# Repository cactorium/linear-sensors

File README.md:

# Linear PCB sensors
This will eventually contain the sensing mechanisms for several different types of digital calipers.
Luckily the patents on all of them have run out, so I can copy a lot of the exact details used in existing calipers, which should mean there's a lot of a better chance of getting good results out of this.
The designs will be made in KiCAD, and will be under a sufficiently liberal license for you guys to use for whatever.
Hopefully these will be cheap and easy enough to use for a lot of interesting applications, like close looping the axes on 3D printers for a lot cheaper than the $1k+ optical scales that's used on higher end models right now.

**NOTE: the schematic and PCB are now in KiCAD 5. I don't know how backwards compatible it is with older version of KiCAD**

## Capacitance-based sensor v1
~The capactive sensor appears to be working right now, with a sample rate of 96 samples/sec and a precision of about ~ +-0.06 mm (~ +-0.002in), limited by noise.
The accuracy appears to stay within +- 0.01mm for a lot of the range, but the inaccuracy increases at various points (and also if you're touching the scale) along its range.
It's currently affected moderately strongly by mains noise, the next revision will add better filtering to the front end to reduce this issue.~
So the signal is actually incredibly accurate, as long as the surfaces are closely mating and the amplifier isn't clipping.
I'm getting about ~0.002 mm precision (still need to check accuracy across the full range) after carefully adjusting gain to remove clipping.
The signal doesn't appear anything near a sine wave at the output, it mainly consists of a lot of sharp spikes that I guess the FIRs turn into something closer to a sine wave.
It's currently probably limited by the numerical accuracy of the arctangent operation in the processing, but I need to do more testing to see how accurate it is across its range before tuning its precision any more.

There also appear to be some large inaccuracies across its full range, which also I'm currently working out.

## Capacitance-based sensor v2
I reduced the width of the scale by half to try to improve the form factor and added a second stage of filtering to try to reduce its susceptibility to noise.
I removed the large metallic layer that used to overlap the receiving pad to see if that would reduce the amount of noise.
I'm pretty sure covering it with ground will reduce the output signal by adding a lot of parasitic capacitance, so right now it's bare aside from a trace to get the signal from the receiving pad.
There's now three stages of amplification, the first one, which is adjustable and has a gain from 1x to 10x, and two fixed stages which are 2x and ~10x respectively.
There's several stages of low pass and high pass filtering throughout all this, plus some bypass resistors in case this all turns out wrong so I can revert to the v1 analog circuitry in the worst case.
The edges of the PCB were also rounded just to make it look a little nicer, and the mounting holes are now evenly spaced to make mechanical stuff a lot easier to work out.

The BOM cost is about $16, which is pretty reasonable, but I'll probably try to get it a little lower next revision.

The extra filter does appear to work very nicely; the output actually looks like a sine wave, so it might be possible to remove some of the digital filtering while maintaining the same accuracy, but I'm going to work on mechanically stabilizing the setup to get more repeatable measurements.
It does appear to be noticeably better just from rough observations; it takes a lot less effort to get the measurement to where it's bouncing around +- 0.001mm compared with the first revision.
I'm guessing the next revision will focus on improving the form factor and cost.

TODO: add pictures

## How they work
Right now I'm looking at two major designs, inductively coupled ones, developed by Mitutoyo, and the T-shaped capacitively coupled ones used in most cheap caliper designs by Mauser-Werke Oberndorf GmbH.
In both cases, the basic gist is that there's a pattern on the stationary bit (called the stator) that affects its coupling with the bit that moves (let's call it the rotor), and in both cases a phase measurement based on measurements as a result of this coupling is used to get a fine measurement, while a counter is used to keep track of how many times the phase has gone about 360 degrees, giving a coarse measurement.
The actual measurement is simply the sum of these two measurements.

In the Mitutoyo design, a pulse is sent into a transmitting coil, which causes it to resonate.
The EM waves produced by this coil are coupled into a pair of receiving coils.
The receiving coils are shaped so that normally the EM waves perfectly cancel out, but the presence and displacement of the disruptors in the stator cause the cancellation to be incomplete.
The receiving coils are shaped so that they form a sine and cosine wave with respect to the displacement relative to the stator.
The receiving coils resonate in series with a capacitor, and a switch is used to stop the resonation near when the voltage across the capacitor is at its peak.
Then the voltage across the capacitors are read using an ADC, and that's used to calculate the displacement within a single stator period.
A counter's used to get the coarser measurement when the stator's moved greater than one period.

In the Mauser-Werke Oberndorf design, there's many transmitting electrodes, each at a different phase.
Each one is shifted by the same amount relative to the one before it.
In the original design, they formed a set of three before it repeated, with relative phases of 0, 120, 240 degrees.
Modern designs tend to use a set of 8, so that's what we'll use here.
These transmitting electrodes couple with the middle of the tee in the stator design, so that the signal read off the T electrode is effectively the capcitively weighted sum of the electrodes that are coupled (physically over) it.
Shifting the rotor causes the ratios to change, allowing an (very good) approximately linear change in phase for a given displacement.
The wider sections of the T are capactively coupled with a receiving electrode on the rotor, and this is filtered and fed into a zero crossing detector to determine the phase different compared with the input signal, giving you a fine measurement of displacement.
The coarse measurement is found by counting, as in the Mitutoyo case.

TODO add patents to repository

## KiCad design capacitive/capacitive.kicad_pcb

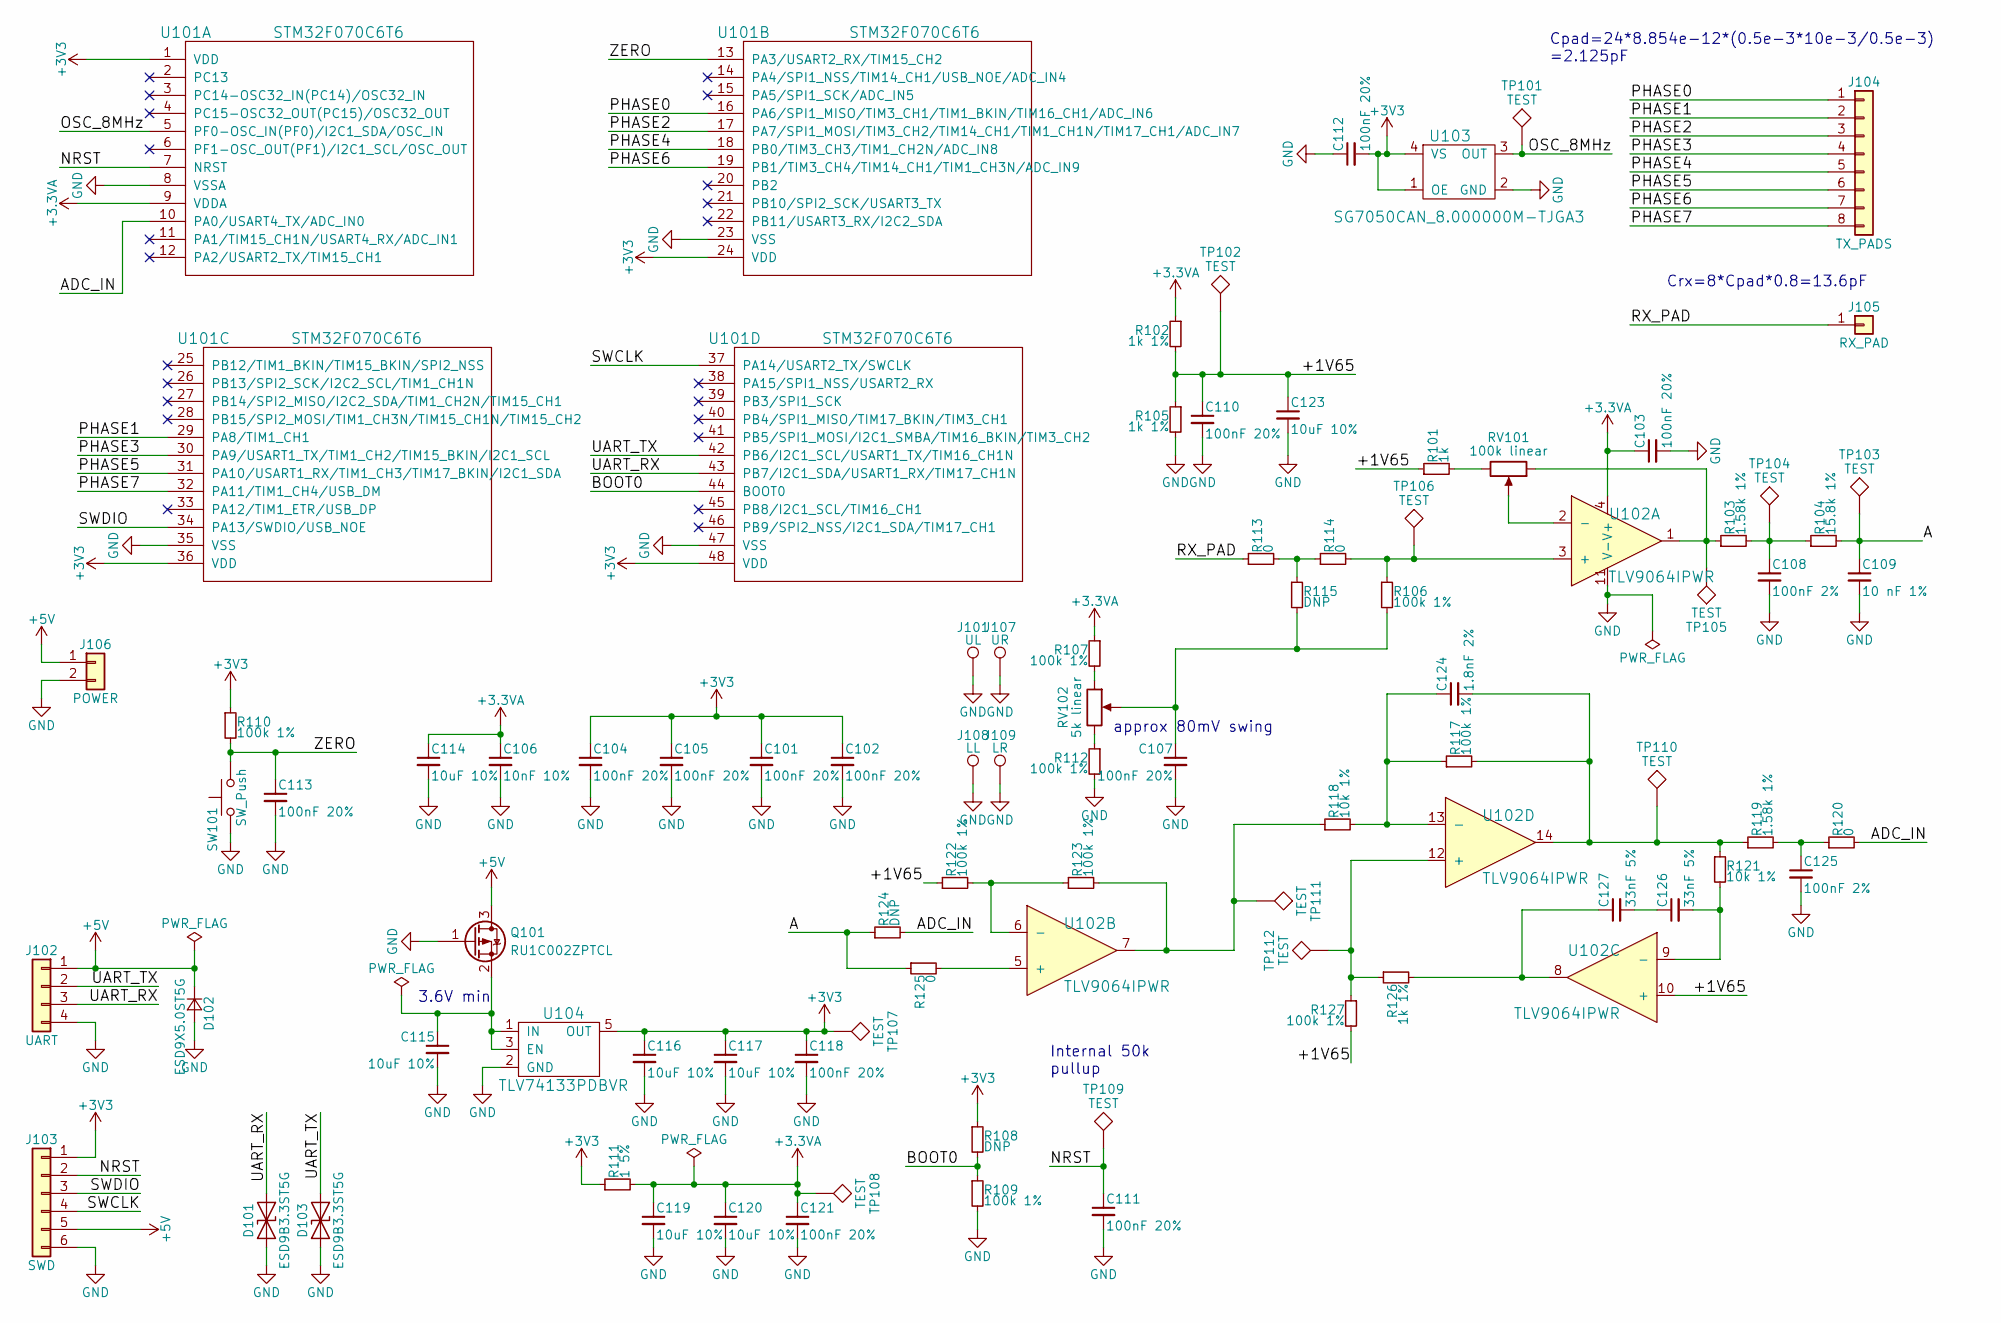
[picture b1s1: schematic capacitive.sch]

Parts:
C101, C102, C103, C104, C105, C107, C110, C111, C112, C113, C118, C121: 100nF 20%; C_0805_HandSoldering; Mouser 710-885012207016
C106: 10nF 10%; R_0603_HandSoldering; Mouser 80-C0603C103M5RAUTO
C108, C125: 100nF 2%; C_1210_HandSoldering; Mouser 667-ECH-U1C104GX5
C109: 10 nF 1%; C_0805_HandSoldering; Mouser 81-GRM2195C1H103FA1D
C114, C115, C116, C117, C119, C120, C123: 10uF 10%; C_1210_HandSoldering; Mouser 581-TAJB106K020RNJV
C124: 1.8nF 2%; C_0603_HandSoldering; Mouser 81-GRM1885C1H182GA1D
C126, C127: 33nF 5%; C_0603_HandSoldering; Mouser 80-C0603C333J4RECLR
D101, D103: ESD9B3.3ST5G; SOD-923; Mouser 863-ESD9B3.3ST5G
D102: ESD9X5.0ST5G; SOD-923; Mouser 863-ESD9X5.0ST5G
J101: UL; Slide_Drill_Left; Mouser NoPart
J102: UART; Socket_Strip_Straight_1x04_Pitch2.54mm; Mouser 855-M20-9990445
J103: SWD; Socket_Strip_Straight_2x03_Pitch2.54mm_SMD; Mouser 855-M20-8750342
J104: TX_PADS; Mouser NoPart
J105: RX_PAD; Mouser NoPart
J106: POWER; Power_Pads; Mouser NoPart
J107: UR; Slide_Drill_Right; Mouser NoPart
J108: LL; Slide_Drill_Left; Mouser NoPart
J109: LR; Slide_Drill_Right; Mouser NoPart
Q101: RU1C002ZPTCL; Rohm_UMT3F; Mouser 755-RU1C001ZPTL
R101: 1k; R_0603_HandSoldering; Mouser 71-CRCW0603100RFKEAC
R102, R105, R126: 1k 1%; R_0402; Mouser 71-CRCW04021K00FKEDC
R103, R119: 1.58k 1%; R_0603_HandSoldering; Mouser 660-RN73H1JTD1581D25
R104: 15.8k 1%; R_0805_HandSoldering; Mouser 71-CRCW12060000Z0EAC
R106, R107, R109, R110, R112, R117, R122, R123, R127: 100k 1%; R_1206_HandSoldering; Mouser 71-CRCW1206100KFKEAC
R108, R115, R124: DNP; R_0603_HandSoldering; Mouser 71-RCS06030000Z0EA
R111: 1 5%; R_0603_HandSoldering; Mouser 755-ESR03EZPJ1R0
R113, R114, R120, R125: 0; R_0805_HandSoldering; Mouser 71-CRCW12060000Z0EAC
R118, R121: 10k 1%; R_0402; Mouser 71-CRCW040210K0FKEDC
RV101: 100k linear; Vishay_T73YE; Mouser 72-T70YE-100K
RV102: 5k linear; Bourns-PVG5H; Mouser 81-PVG5H502C03B00
SW101: SW_Push; LL3301NF065QG; Mouser 612-LL3301NF065QG
TP101, TP102, TP103, TP104, TP105, TP106, TP107, TP108, TP109, TP110, TP111, TP112: TEST; Measurement_Point_Round-SMD-Pad_Small; Mouser NoPart
U101: STM32F070C6T6; ST_LQFP48; Mouser 511-STM32F070C6T6
U102: TLV9064IPWR; TI_TSSOP14; Mouser 595-TLV9064IPWR
U103: SG7050CAN_8.000000M-TJGA3; Crystal_SMD_7050-4pin_7.0x5.0mm; Mouser 732-7050CA8.00TJGA3
U104: TLV74133PDBVR; SOT-23-5_HandSoldering; Mouser 595-TLV74133PDBVR

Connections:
+3.3VA: C103.1, C106.1, C114.1, C119.1, C120.1, C121.1, R102.1, R107.1, R111.2, TP108.1, U101.9 (VDDA), U102.4 (V+)
+3V3: C101.1, C102.1, C104.1, C105.1, C112.2, C116.1, C117.1, C118.1, J103.1, R108.1, R110.1, R111.1, TP107.1, U101.1 (VDD), U101.24 (VDD), U101.36 (VDD), U101.48 (VDD), U103.1 (OE), U103.4 (VS), U104.5 (OUT)
+5V: D102.1 (K), J102.1, J103.5, J106.1, Q101.3 (D)
/+1V65: C110.1, C123.1, R101.1, R102.2, R105.1, R122.1, R127.2, TP102.1, U102.10 (+)
/A: C109.1, R104.2, R124.1, R125.1, TP103.1
/ADC_IN: R120.2, R124.2, U101.10 (PA0/USART4_TX/ADC_IN0)
/BOOT0: R108.2, R109.1, U101.44 (BOOT0)
/NRST: C111.1, J103.2, TP109.1, U101.7 (NRST)
/OSC_8MHz: TP101.1, U101.5 (PF0-OSC_IN(PF0)/I2C1_SDA/OSC_IN), U103.3 (OUT)
/PHASE0: J104.1, U101.16 (PA6/SPI1_MISO/TIM3_CH1/TIM1_BKIN/TIM16_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)
/PHASE1: J104.2, U101.29 (PA8/TIM1_CH1)
/PHASE2: J104.3, U101.17 (PA7/SPI1_MOSI/TIM3_CH2/TIM14_CH1/TIM1_C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)
/PHASE3: J104.4, U101.30 (PA9/USART1_TX/TIM1_CH2/TIM15_BKIN/I2C1_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)
/PHASE4: J104.5, U101.18 (PB0/TIM3_CH3/TIM1_CH2N/ADC_IN8)
/PHASE5: J104.6, U101.31 (PA10/USART1_RX/TIM1_CH3/TIM17_BKIN/I2C1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)
/PHASE6: J104.7, U101.19 (PB1/TIM3_CH4/TIM14_CH1/TIM1_CH3N/ADC_IN9)
/PHASE7: J104.8, U101.32 (PA11/TIM1_CH4/USB_DM)
/RX_PAD: J105.1, R113.1
/SWCLK: J103.4, U101.37 (PA14/USART2_TX/SWCLK)
/SWDIO: J103.3, U101.34 (PA13/SWDIO/USB_NOE)
/UART_RX: D101.1 (A1), J102.3, U101.43 (PB7/I2C1_SDA/USART1_RX/TIM17_CH1N)
/UART_TX: D103.1 (A1), J102.2, U101.42 (PB6/I2C1_SCL/USART1_TX/TIM16_CH1N)
/ZERO: C113.1, R110.2, SW101.1, U101.13 (PA3/USART2_RX/TIM15_CH2)
GND: C101.2, C102.2, C103.2, C104.2, C105.2, C106.2, C107.2, C108.2, C109.2, C110.2, C111.2, C112.1, C113.2, C114.2, C115.2, C116.2, C117.2, C118.2, C119.2, C120.2, C121.2, C123.2, C125.2, D101.2 (A2), D102.2 (A), D103.2 (A2), J101.1, J102.4, J103.6, J106.2, J107.1, J108.1, J109.1, Q101.1 (G), R105.2, R109.2, R112.2, SW101.2, U101.8 (VSSA), U101.23 (VSS), U101.35 (VSS), U101.47 (VSS), U102.11 (V-), U103.2 (GND), U104.2 (GND)
unnamed: C107.1, R106.2, R115.2, RV102.2
unnamed: C108.1, R103.2, R104.1, TP104.1
unnamed: C115.1, Q101.2 (S), U104.1 (IN), U104.3 (EN)
unnamed: C124.1, R117.1, R118.2, U102.13 (-)
unnamed: C124.2, R117.2, R119.1, R121.1, TP110.1, U102.14
unnamed: C125.1, R119.2, R120.1
unnamed: C126.1, C127.2
unnamed: C126.2, R121.2, U102.9 (-)
unnamed: C127.1, R126.2, U102.8
unnamed: R101.2, RV101.3
unnamed: R103.1, RV101.1, TP105.1, U102.1
unnamed: R106.1, R114.2, TP106.1, U102.3 (+)
unnamed: R107.2, RV102.1
unnamed: R112.1, RV102.3
unnamed: R113.2, R114.1, R115.1
unnamed: R118.1, R123.2, TP111.1, U102.7
unnamed: R122.2, R123.1, U102.6 (-)
unnamed: R125.2, U102.5 (+)
unnamed: R126.1, R127.1, TP112.1, U102.12 (+)
unnamed: RV101.2, U102.2 (-)

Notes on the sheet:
3.6V min
Cpad=24*8.854e-12*(0.5e-3*10e-3/0.5e-3) =2.125pF
Crx=8*Cpad*0.8=13.6pF
Internal 50k pullup
approx 80mV swing

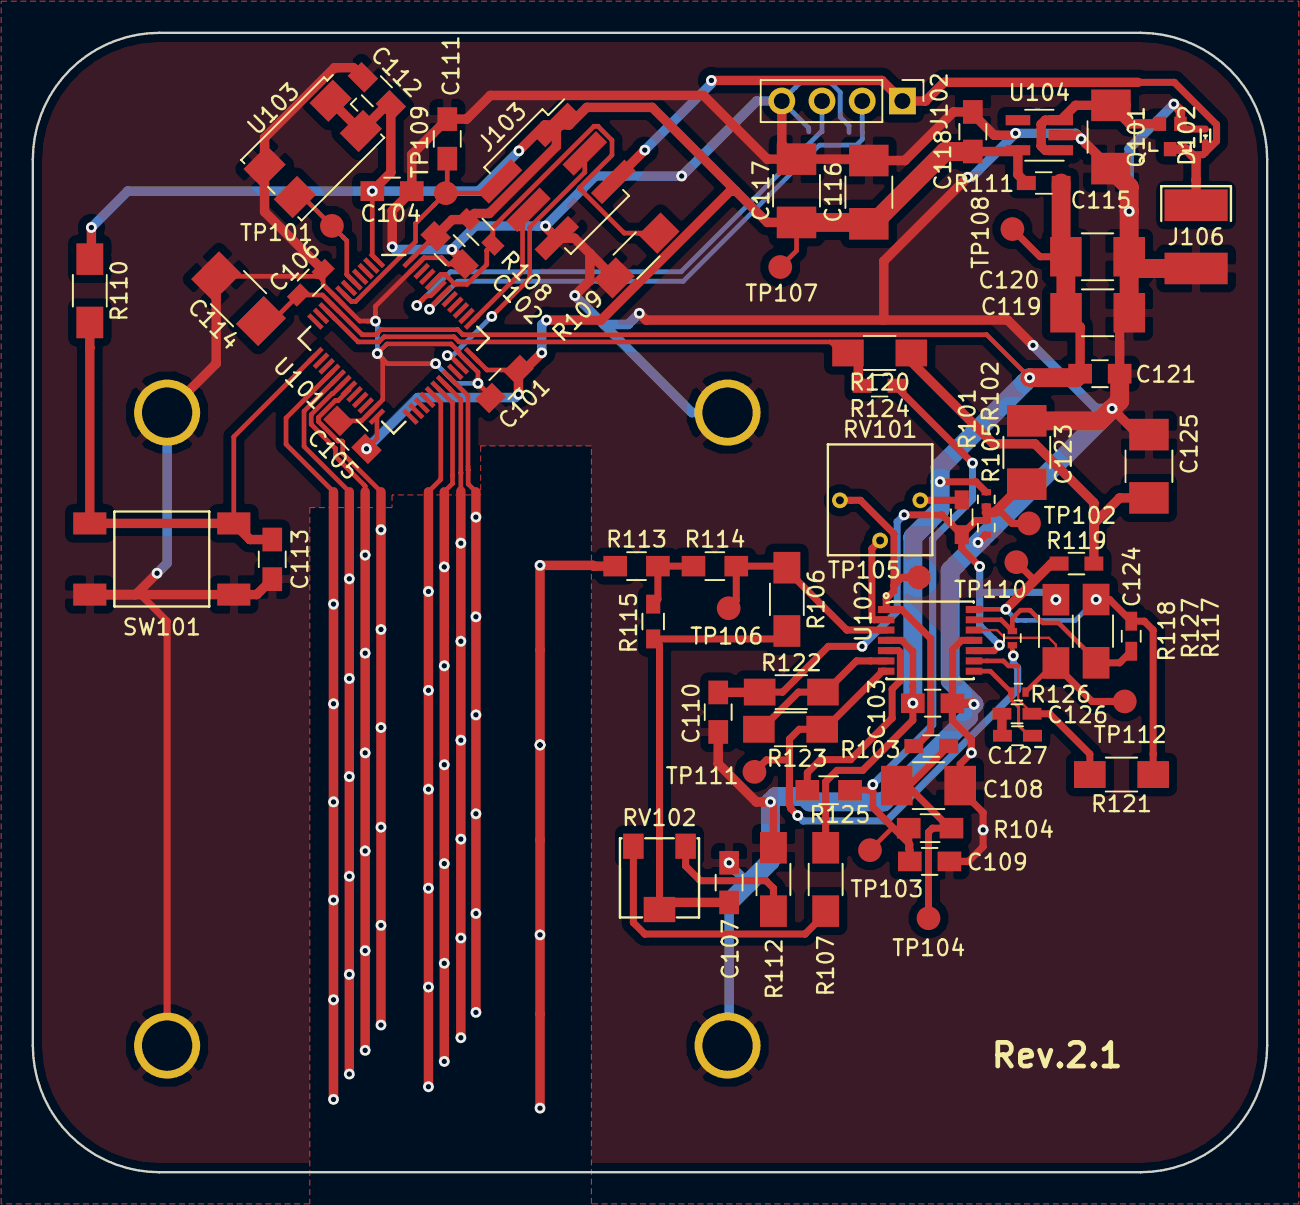
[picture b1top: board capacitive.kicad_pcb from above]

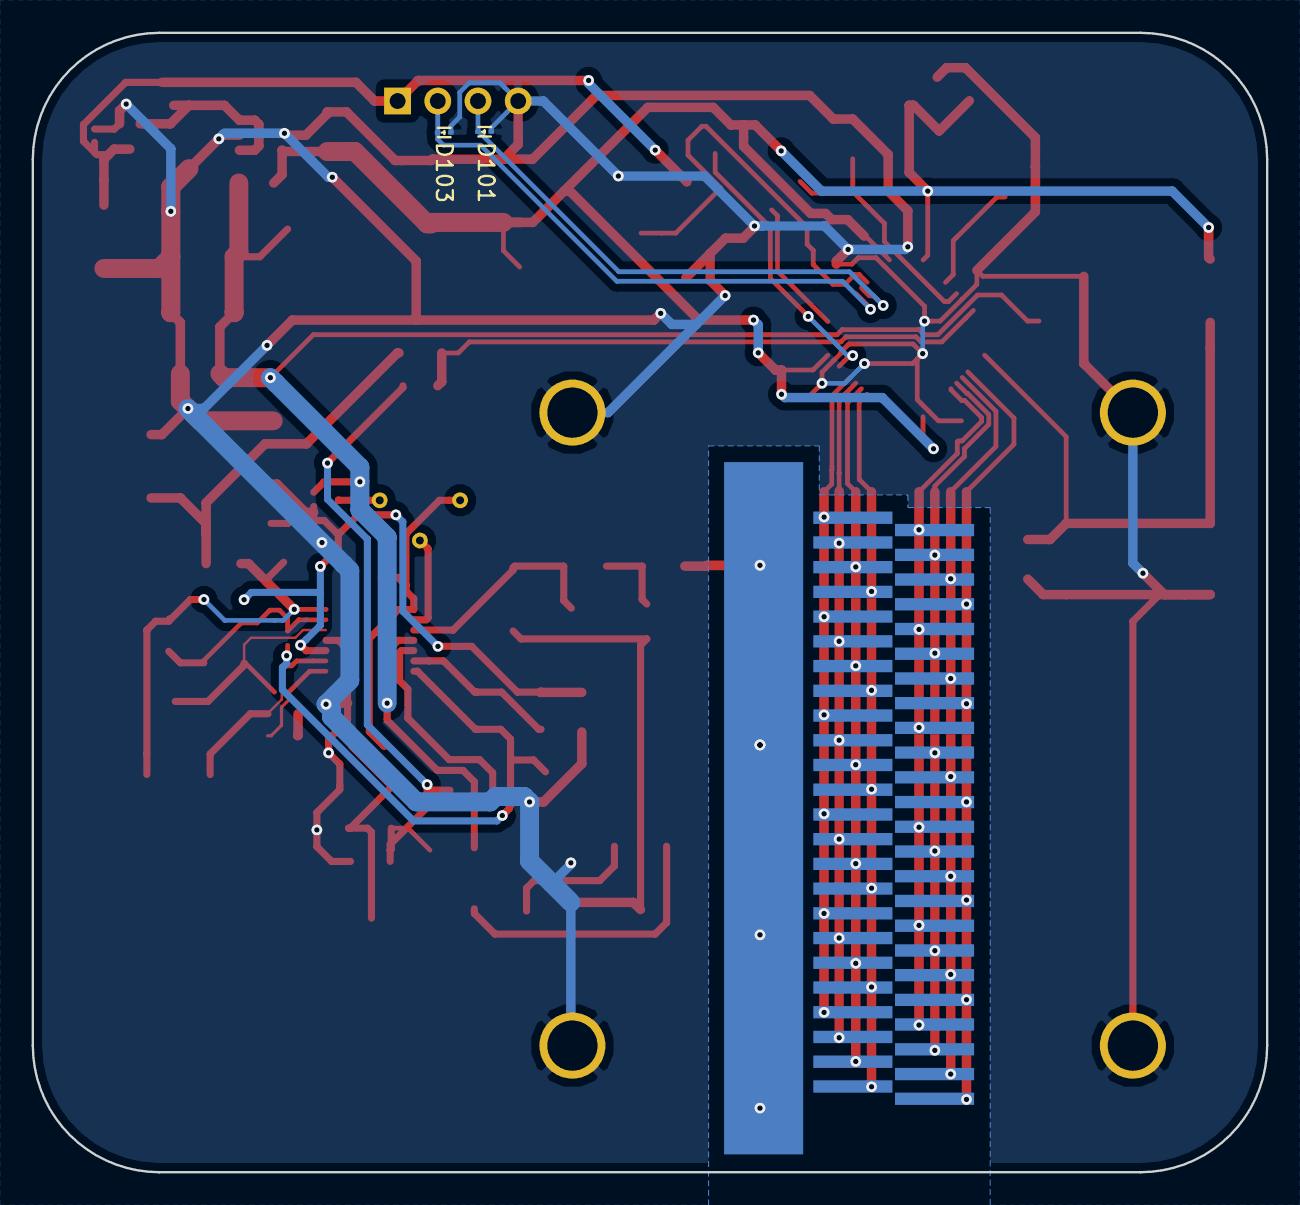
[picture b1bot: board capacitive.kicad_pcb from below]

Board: 2 copper layers, 78.0 x 72.0 mm, 84 parts (4 on the bottom side), 44 nets.

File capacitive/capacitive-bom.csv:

Reference,Quantity,Identifier,Package,Value,Tolerance,Voltage,Current,Power,PN,Mouser
"U101","1","","","STM32F070C6T6","","","","","","511-STM32F070C6T6"
"C111;C103;C110;C101;C104;C105;C102;C118;C121;C112;C113;C107","12","","","100nF 20%","","","","","","710-885012207016"
"R103;R119","2","","","1.58k 1%","","","","","","660-RN73H1JTD1581D25"
"C108;C125","2","","","100nF 2%","","","","","","667-ECH-U1C104GX5"
"C109","1","","","10 nF 1%","","","","","","81-GRM2195C1H103FA1D"
"R105;R126;R102","3","","","1k 1%","","","","","","71-CRCW04021K00FKEDC"
"R108;R115;R124","3","","","DNP","","","","","","71-RCS06030000Z0EA"
"J102","1","","","UART","","","","","","855-M20-9990445"
"J103","1","","","SWD","","","","","","855-M20-8750342"
"C106","1","","","10nF 10%","","","","","","80-C0603C103M5RAUTO"
"R101","1","","","100","","","","","","71-CRCW0603100RFKEAC"
"RV101","1","","","100k linear","","","","","","72-T70YE-100K"
"R106;R109;R110;R112;R107;R127;R117;R121;R123;R122","10","","","100k 1%","","","","","","71-CRCW1206100KFKEAC"
"C120;C116;C117;C119;C115;C114;C123","7","","","10uF 10%","","","","","","581-TAJB106K020RNJV"
"J106","1","","","POWER","","","","","","NoPart"
"TP108;TP107;TP106;TP105;TP104;TP103;TP101;TP109;TP102;TP111;TP112;TP110","12","","","TEST","","","","","","NoPart"
"U103","1","","","SG7050CAN_8.000000M-TJGA3","","","","","","732-7050CA8.00TJGA3"
"U104","1","","","TLV74133PDBVR","","","","","","595-TLV74133PDBVR"
"J104","1","","","TX_PADS","","","","","","NoPart"
"J105","1","","","RX_PAD","","","","","","NoPart"
"SW101","1","","","SW_Push","","","","","","612-LL3301NF065QG"
"R111","1","","","1 5%","","","","","","755-ESR03EZPJ1R0"
"Q101","1","","","RU1C002ZPTCL","","","","","","755-RU1C001ZPTL"
"D102","1","","","ESD9X5.0ST5G","","","","","","863-ESD9X5.0ST5G"
"RV102","1","","","5k linear","","","","","","81-PVG5H502C03B00"
"J108","1","","","LL","","","","","","NoPart"
"J109","1","","","LR","","","","","","NoPart"
"J107","1","","","UR","","","","","","NoPart"
"J101","1","","","UL","","","","","","NoPart"
"D101;D103","2","","","ESD9B3.3ST5G","","","","","","863-ESD9B3.3ST5G"
"R113;R114;R125;R120","4","","","0","","","","","","71-CRCW12060000Z0EAC"
"R104","1","","","15.8k 1%","","","","","","667-ERJ-8ENF1582V"
"U102","1","","","TLV9064IPWR","","","","","","595-TLV9064IPWR"
"R118","1","","","10k 1%","","","","","","71-CRCW040210K0FKEDC"
"C124","1","","","1.8nF 2%","","","","","","81-GRM1885C1H182GA1D"
"C126;C127","2","","","33nF 5%","","","","","","80-C0603C333J4RECLR"

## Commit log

2018-04-04 Write transmit loop simulation
2018-04-04 Fix various things, TODO swap names
2018-04-04 Rename to reflect actual usage
2018-04-04 Fix bugs
2018-04-04 Remove extra file
2018-04-04 Reorganize slightly
2018-04-04 Add README
2018-04-04 Fix width of receiving coil
2018-04-04 Fix width on multithreaded version
2018-04-04 Fix x coordinates in RX sim
2018-04-04 Remove accidentally added file
2018-04-04 Fix stuff in tx
2018-04-04 Save new data, add script for building multhreaded transmit sim
2018-04-04 Add collected simulation data
2018-04-04 Improve rx multithreaded case by caching path calculations
2018-04-05 Reduce grid resolution to see if the simulated inductance values have converged
2018-04-20 Finish most of schematic and start work on antenna designs; specified dimensions for receiving antenna appear to be unmanufacturable
2018-04-21 Start work on capactive sensor
2018-05-15 Start simulating parts of the design to optimize stuff
2018-05-15 Start work on schematic
2018-05-18 Tweak simulations a bit TODO switch to Python
2018-05-18 Test new filter
2018-05-19 Schematic capture basically finished; TODO source and fp all components
2018-05-19 Remove linear regulator and replace with resistor
2018-05-19 Write script to autofill components; save before test
2018-05-19 Autofill works!
2018-05-19 Output list of components with missing footprints
2018-05-19 Improve autofill output
2018-05-19 Fix terminology
2018-05-19 Add some footprints
2018-05-20 Generate TI SOIC-8 footprint
2018-05-20 Output components missing distributor data
2018-05-20 Refactor out some functionality from main()
2018-05-20 Everything footprinted except for the scale coupling pads
2018-05-20 Autofill components
2018-05-20 Start work on caliper scale generation
2018-05-20 Ignore pycache and correct for gap between scale bases in capacitance calculation
2018-05-20 Working scale generator
2018-05-20 Add scales to generator script
2018-05-21 Add generation for holes
2018-05-22 Generate first revision Gerber files
2018-05-23 Add input capacitor to help set the input roll-off frequency; it seems to reduce ripple a fair amount
2018-05-24 Regenerate schematic PDF
2018-05-24 Extend board 2mm to improve mechanical strength of left drill holes and improve ground stitching under MCU
2018-05-24 Generate scale outline helper
2018-05-24 Generate sensor scale
2018-06-23 Write zip generating files
2018-06-23 Generate BOM
2018-07-01 Fix mouser BOM generation, add in notes from current testing
2018-07-13 Add OpenOCD config
2018-07-14 First attempt at building
2018-07-14 Getting used to libopencm3 stuff
2018-07-14 Test signal is working! Apparently the GPIO module has to have a clock before you can use it
2018-07-14 Working pulse generation
2018-07-14 Add in some spots to experiment with filtering in the future
2018-07-14 Shave off about 140 bytes by simplifying GPIO setup
2018-07-14 Update schematic a bit
2018-07-14 Test UART; works!
2018-07-14 Working ADC data collection example
2018-07-14 Collect data
2018-07-14 Add more data; datasets 11-15 are at the weird signal weak point
2018-07-14 Visualize data
2018-07-14 Experiment with FIR parameters; current best is 128 tap high pass followed by a 64 tap low pass
2018-07-15 Add a second LP cascade; performance improved noticeably
2018-07-15 Synchronize ADC timing with the pulses
2018-07-15 Switch USART to nonblocking FSM
2018-07-15 Generate plots of data
2018-07-15 Mark new best filter (it's been the best for a while, just forgot to fix the comment
2018-07-15 Move ADC processing into main loop
2018-07-15 Test filter cascade reordering; performance not affect, as expected
2018-07-15 Restructure so the buffer logic is in main
2018-07-15 Move a lot of files around and add README
2018-07-15 Remove old data directory
2018-07-15 Move data
2018-07-15 Working C filter; type demotion is annoying
2018-07-15 Add FIR filter, start work on adding phase calculation
2018-07-15 Fix return type in FIR function
2018-07-15 Add trig functions kind of
2018-07-16 Optimize code to stop overrun
2018-07-16 Kind of working; IQ data looks bad, lots of overrun still
2018-07-16 Well it's not overflowing right now; save point in case I want to continue trying to do all the calculations offline; TODO explore ADC duty cycling; collect for five cycles while processing over ten 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
2018-07-16 Test and verify IQ logic
2018-07-16 Accuracy is about 0.03 mm; need to get rid of more of the noise
2018-07-16 Print out position data on USART TODO verify measurement accuracy
2018-07-16 Update READMEs
2018-07-17 Add zeroing mode
2018-07-18 Remove extra USART stuff, improve README
2018-07-19 Add second stage of filtering
2018-07-20 Save before autofill
2018-07-20 Autofill first time
2018-07-20 All parts sourced and netlist generated
2018-07-21 Change scale size and finish relayout
2018-07-21 Relayout capacitive scale and regenerate all Gerber files
2018-07-21 Regenerate Mouser BOM and fix Mouser BOM gen bug
2018-07-21 Swap out MOSFET to RU1C001ZP
2018-07-21 Add updated BOM
2018-07-21 Fix reverse voltage MOSFET probably
2018-07-24 Regenerate Gerbers (didn't actually need to)
2018-07-24 Remove stuff from old Gerber files and fix zipfiles
2018-08-03 Convert over to Kicad 5, fix mistakes for next revision
2018-08-03 Regenerate all output files and update README
2018-08-03 Move capacitor so it doesn't cover some designators
2018-08-04 Flip offset pot around to make it more accessible TODO maybe remove offset pot to save cost
2019-06-30 Explore IIR filters; it seems like FIR windowing will have to do
